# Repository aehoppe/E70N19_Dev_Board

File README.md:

# E70N19_Dev_Board
 Repository for developing an ATSAME70N19-based dev board for Eclectronics FA 2017

## Brief Description of Board Design

Currently the board is designed to fit onto a 10cm X 10cm PCB. We will be using female header pins, much like an Arduino, on opposite edges of the PCB. 

## Changes to Schematic & BOM

There were no changes to the BOM.

The schematic had a few modifications based on feedback we received.

- Adding a voltage divider to TPS2112A to prevent brown out
- Added load capacitors to our RTC crystal
- Added a 10uF to BM71
- Added power LED to show status of power
- Changed nRST button to drive it to ground instead of power
- Added 30Ohm resistors to USB data lines
- Added connections to ground, 3v3 and VBUS to connectors

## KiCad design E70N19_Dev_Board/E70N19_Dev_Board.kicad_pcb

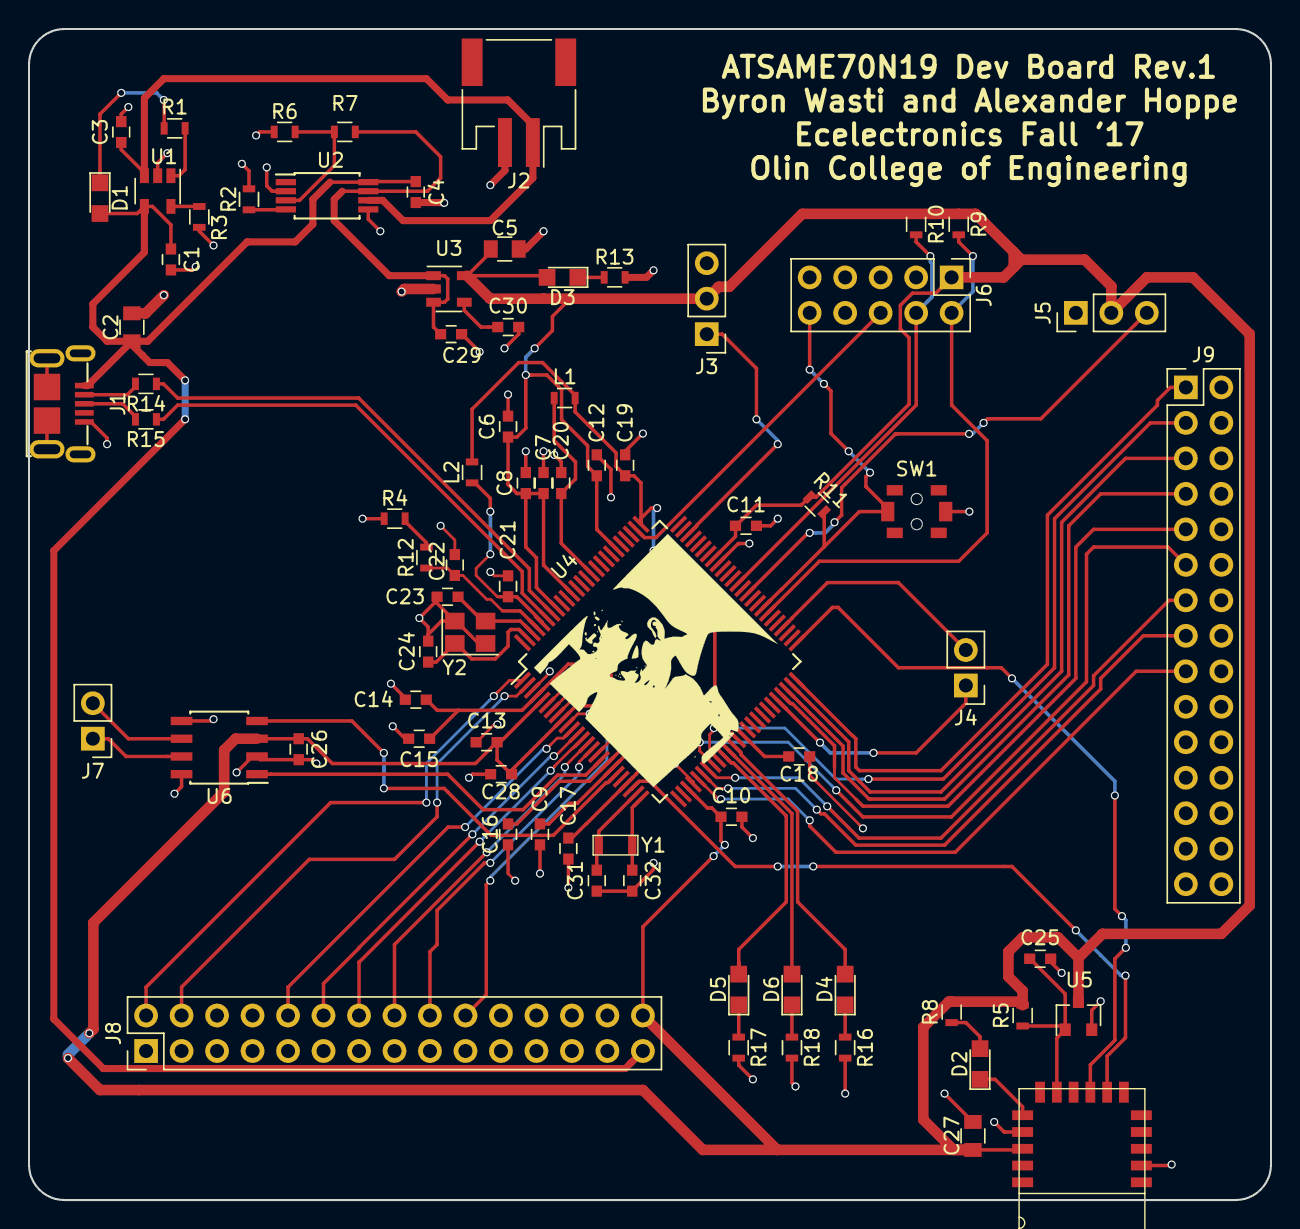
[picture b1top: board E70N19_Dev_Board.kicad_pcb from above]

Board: 2 copper layers, 88.9 x 83.8 mm, 77 parts (0 on the bottom side), 65 nets.

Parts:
C1, C3, C6: 4.7uF; C_0603
C2, C5, C27: 10uF; C_0805
C4: 0.1uF; C_0603
C7, C8, C9, C10, C11, C12, C13, C15, C16, C17, C18, C19, C20, C21, C26, C28, C29: 100nF; C_0603
C14, C25: 1uF; C_0603
C22: 10pF; C_0603
C23, C24: 18pF; C_0603
C30: 10nF; C_0603
C31, C32: 12.5pF; C_0603
D1, D2, D3: LED; LED_0805
D4, D5, D6: LED_Small; LED_0805
FP1: BM71BLES1FC2
J1: USB_microB_2040002-1
J2: Battery 1x2; JST_PH_S2B-PH-SM4-TB_02x2.00mm_Angled
J3: JTAGSEL_JUMPER 1x3; Pin_Header_Straight_1x03_Pitch2.54mm
J4: UART_PROG 1x2; Pin_Header_Straight_1x02_Pitch2.54mm
J5: ERASE_JUMPER 1x3; Pin_Header_Straight_1x03_Pitch2.54mm
J6: ARM-Cortex-Debug-10; Pin_Header_Straight_2x05_Pitch2.54mm
J7: CAN 1x2; Pin_Header_Straight_1x02_Pitch2.54mm
J8, J9: Conn_02x15_Counter_Clockwise; Pin_Header_Straight_2x15_Pitch2.54mm
L1, L2: 470R @ 100MHz; R_0603
R1: 475; R_0603
R2, R8: 402; R_0603
R3: 2K; R_0603
R4: 4.99K; R_0603
R5: 4.75K; R_0603
R6: 10K; R_0603
R7: 20K; R_0603
R9, R10, R11: 100K; R_0603
R12: 63.4; R_0603
R13, R16, R17, R18: 1K; R_0603
R14, R15: 30; R_0603
SW1: NRST_BUTTON; PTS820_J15M_SMTR_LFS
U1: MCP73831; SOT-23-5
U2: TPS2112A; TSSOP-8_4.4x3mm_Pitch0.65mm
U3: SPX3819M5-L-3-3; SOT-23-5
U4: ATSAME70N19; LQFP-100_14x14mm_Pitch0.5mm
U5: RT9818A-18GV; SOT-23
U6: SN65HVD233-Q1; SOIC-8_3.9x4.9mm_Pitch1.27mm
Y1: Crystal_Small; ECS-.327-12.5-34B-TR
Y2: Crystal; Crystal_SMD_SeikoEpson_FA238-4pin_3.2x2.5mm

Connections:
+3V3: C5.1, C6.1, C7.1, C8.1, C9.1, C10.1, C11.1, C12.1, C13.1, C26.1, C27.1, C28.1, D3.2, FP1.14, J3.2, J5.2, J6.1, J8.30, R5.1, R8.1, R9.1, R10.1, R11.1, U3.5, U4.5, U4.9, U4.19, U4.28, U4.68, U4.81, U4.90, U4.93, U5.3, U6.3
/CAN_RX: U4.20, U6.4
/CAN_TX: U4.17, U6.1
/D+: J1.3, R15.2
/D-: J1.2, R14.2
/D_N: R14.1, U4.94
/D_P: R15.1, U4.95
/NRST: J6.10, R11.2, SW1.2, U4.58
/PA12: J9.7, U4.48
/PA14: J9.3, U4.34
/PA15: J9.11, U4.33
/PA16: J9.17, U4.30
/PA17: J8.20, U4.16
/PA18: J8.18, U4.15
/PA19: J8.16, U4.14
/PA20: J8.14, U4.13
/PA23: J9.15, U4.31
/PA27: J9.1, U4.50
/PB0: J8.12, U4.12
/PB1: J8.10, U4.11
/PD0: J8.2, U4.1
/PD18: J9.5, U4.49
/PD19: J9.9, U4.47
/PD27: J9.13, U4.32
/PD31: J8.4, U4.2
/TCK: J6.4, R10.2, U4.63
/TDO: J6.6, U4.77
/TMS: J6.2, R9.2, U4.57
/VBUS: C1.1, C2.1, C4.1, D1.2, J1.1, J8.29, U1.4, U2.8
GND: C1.2, C2.2, C3.2, C4.2, C5.2, C6.2, C7.2, C8.2, C9.2, C10.2, C11.2, C12.2, C13.2, C14.2, C15.2, C16.2, C17.2, C18.2, C19.2, C20.2, C21.2, C22.2, C23.2, C24.2, C25.2, C26.2, C27.2, C28.2, C29.2, C30.2, C31.2, C32.2, FP1.2, FP1.13, J1.5, J1.6, J1.7, J1.8, J1.9, J1.10, J1.11, J2.2, J6.3, J6.5, J8.26, J8.27, J8.28, R2.2, R3.2, R4.1, R6.1, R13.2, R16.2, R17.2, R18.2, SW1.1, U1.2, U2.2, U2.5, U3.2, U4.3, U4.6, U4.7, U4.8, U4.10, U4.29, U4.67, U5.2, U6.2, U6.5, U6.8, Y2.2, Y2.4
unnamed: C3.1, J2.1, U1.3, U2.6
unnamed: C14.1, C15.1, C16.1, C17.1, C18.1, C19.1, L1.2, L2.2, U4.4, U4.18, U4.22, U4.39, U4.76
unnamed: C20.1, L1.1, U4.86
unnamed: C21.1, L2.1, U4.96
unnamed: C22.1, R12.1, U4.97
unnamed: C23.1, U4.98, Y2.3
unnamed: C24.1, U4.99, Y2.1
unnamed: C25.1, FP1.10, R5.2, U5.1
unnamed: C29.1, R7.1, U2.7, U3.1, U3.3
unnamed: C30.1, U3.4
unnamed: C31.1, U4.24, Y1.1
unnamed: C32.1, U4.25, Y1.2
unnamed: D1.1, R1.2
unnamed: D2.1, FP1.12
unnamed: D2.2, R8.2
unnamed: D3.1, R13.1
unnamed: D4.1, R16.1
unnamed: D4.2, U4.37
unnamed: D5.1, R17.1
unnamed: D5.2, U4.35
unnamed: D6.1, R18.1
unnamed: D6.2, U4.36
unnamed: FP1.7, U4.23
unnamed: FP1.8, U4.51
unnamed: J3.1, U4.73
unnamed: J4.1, U4.46
unnamed: J4.2, U4.54
unnamed: J5.3, U4.61
unnamed: J7.1, U6.7
unnamed: J7.2, U6.6
unnamed: R1.1, U1.1
unnamed: R2.1, U2.4
unnamed: R3.1, U1.5
unnamed: R6.2, R7.2, U2.3
unnamed: R4.2, R12.2

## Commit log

2017-09-28 Library and Schematic development
2017-09-28 added/edited bluetooth module
2017-09-28 Fixing up library
2017-09-28 Merged ATSAME70N19 library
2017-09-29 Begun power connections on ATSAME70N19
2017-10-01 Added 3V3 compliant CAN TXRX
2017-10-01 Added descriptions to all libraries
2017-10-01 Implements power schematic
2017-10-02 Finished Schematic
2017-10-02 Updating schematic with corrected values
2017-10-02 Finishing BoM and other requirements
2017-10-02 Adds PDF schematic
2017-10-06 Fixing up schematic based on design review notes
2017-10-07 Began associating footprints
2017-10-07 Hoppe did not save correctly
2017-10-07 Fixing schematic error
2017-10-07 Brad's micro OTG connector
2017-10-07 More footprints
2017-10-07 Fixing footprint for BLE module
2017-10-08 Added tactile switch footprint
2017-10-08 Finishing PCB component placement
2017-10-08 Added debug LEDs
2017-10-11 Initial routing
2017-10-12 Beginning to route
2017-10-12 Updated README with changes
2017-10-12 Edited schematic to make pin fanout easier
2017-10-12 Primary four layer fanout
2017-10-12 More excape routing
2017-10-12 Updated with new schematic
2017-10-12 Finishing double layer board
2017-10-12 Fixed up fanout connections
2017-10-12 Added hoppe bmp
2017-10-12 finishing touches
2017-10-12 Adding Hoppe's face
2017-10-12 Revert "finishing touches"
    This reverts commit 4a8290c698ae611552ebb1913fe9187be52cce0b.
2017-10-16 Fixing unconnected ground nets
2017-10-17 Fixing missing uC footprint
2017-10-17 No rat lines
2017-10-26 Edited schematic to reflect PMUX rework
2017-10-26 Add zip of atmel START files
2017-10-26 Inflated atmel START files
2017-10-27 Tried to make IO pin LEDs flash
2017-11-27 Fix library issues
2017-11-27 Writeup of lessons learned from this project
2017-11-27 Revise lessons learned
2017-11-27 Add Pandoc header
